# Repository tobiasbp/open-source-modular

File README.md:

# open-source-modular
Repository for the synthesizer project at www.open-source-modular.com

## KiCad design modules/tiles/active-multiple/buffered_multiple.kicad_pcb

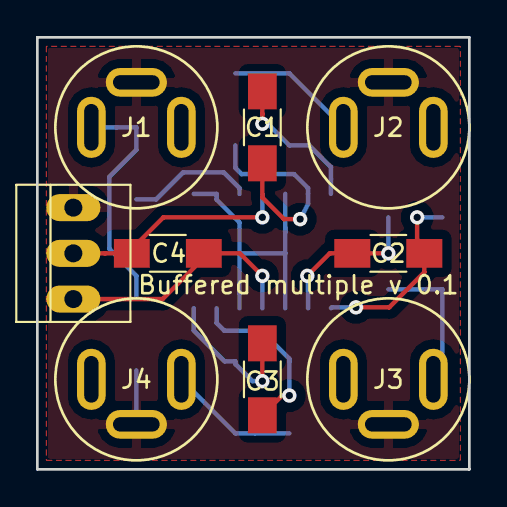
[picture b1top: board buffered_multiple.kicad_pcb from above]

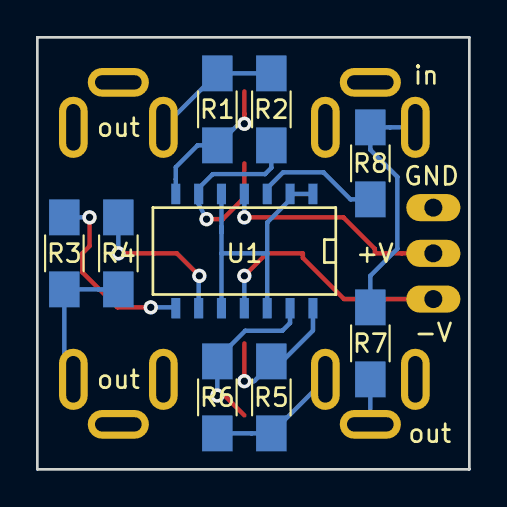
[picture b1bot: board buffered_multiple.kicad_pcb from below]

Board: 2 copper layers, 24.0 x 24.0 mm, 18 parts (9 on the bottom side), 15 nets.

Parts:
C1, C2, C3: 100pF; C_1206_HandSoldering
C4: 100nF; C_1206_HandSoldering
J1: InputJack1; PJ392-3.5mm-jack-vertical-SRT
J2: OutputJack1; PJ392-3.5mm-jack-vertical-SRT
J3: OutputJack2; PJ392-3.5mm-jack-vertical-SRT
J4: OutputJack3; PJ392-3.5mm-jack-vertical-SRT
J5: power_supply; PINHEAD1-3
R1, R3, R5: 220; R_1206_HandSoldering
R2, R4, R6: 4.7K; R_1206_HandSoldering
R7: 100K; R_1206_HandSoldering
R8: 1K; R_1206_HandSoldering
U1: TL074; SOIC-14_N

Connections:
+12V: C4.1, J5.2, U1.4
-12V: C4.2, J5.1, U1.11
GND: J1.S, J2.S, J3.S, J4.S, J5.3, R7.1
unnamed: C1.1, R1.1, U1.7
unnamed: C1.2, R2.2, U1.6
unnamed: C2.1, R3.1, U1.8
unnamed: C2.2, R4.2, U1.9
unnamed: C3.1, R5.1, U1.14
unnamed: C3.2, R6.2, U1.13
unnamed: J1.T, R7.2, R8.2
unnamed: R8.1, U1.3
unnamed: U1.1, U1.2, U1.5, U1.10, U1.12
output_1: J2.T, R1.2, R2.1
output_2: J3.T, R3.2, R4.1
output_3: J4.T, R5.2, R6.1

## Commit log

2022-10-10 Moved active multiple to own dir
2022-10-10 moved fp-lib-table for buffered-multiple
2022-10-10 removed active-multiple as files in this repo
